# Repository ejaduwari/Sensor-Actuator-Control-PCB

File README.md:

# Sensor-Actuator-Control-PCB
STM32F103C8 carrier board controlling 6 stepper motors, servos, limit switches, and IO expanders with UART, SPI, and I2C interfaces. Includes full pin mapping, dual-regulator power design, and detailed failure analysis with debugging insights and hardware lessons learned.

# 📘 STM32F103C8 Stepper Motor Controller  
### Carrier Board + Small Pill Architecture & Debug Report

---

## 📑 Table of Contents
- [Overview](#overview)
- [Hardware Architecture](#hardware-architecture)
- [Pin Mapping (STM32 ↔ Carrier Board)](#pin-mapping-stm32--carrier-board)
- [Peripheral Interfaces](#peripheral-interfaces)
- [Clock & Crystal](#clock--crystal)
- [Power System Design](#power-system-design)
- [IO Expanders](#io-expanders)
- [Failure Report & Debugging](#failure-report--debugging)
- [Root Cause Analysis](#root-cause-analysis)
- [Current Status](#current-status)
- [Design Lessons & Prevention](#design-lessons--prevention)

---

## 🔍 Overview

This project is a **custom STM32F103C8-based PCB** designed to control:
- Multiple **A4988 stepper drivers**
- Several **servo outputs**
- External IO via expanders

The board uses a **Small Pill (STM32F103C8T6)** mounted on a **carrier board**, providing structured routing for motion control and expansion.

---

## 🧩 Hardware Architecture

- **MCU:** STM32F103C8T6 (Small Pill)
- **Motor Drivers:** A4988 (external)
- **IO Expansion:** PI4IOE5V6416
- **Power Inputs:**
  - USB (via L78L00 regulator)
  - External 5V (via AP2112K-3.3)
- **Control Signals:**
  - STEP / DIR for 6 axes
  - Servo PWM outputs
- **Debug Interface:**
  - SWD (SWCLK, SWDIO)

---

## 🔌 Pin Mapping (STM32 ↔ Carrier Board)

| STM32 Pin | Function |
|----------|--------|
| PA0 | 5_DIR |
| PA1 | 5_STP |
| PA2 | TX |
| PA3 | RX |
| PA4 | 1_DIR |
| PA5 | SCK |
| PA6 | MISO |
| PA7 | MOSI |
| PA8 | SERVO_1_3V3 |
| PA9 | SERVO_2_3V3 |
| PA10 | SERVO_3_3V3 |
| PA11 | USB- |
| PA12 | USB+ |
| PA15 | SERVO_4_3V3 |

| STM32 Pin | Function |
|----------|--------|
| PB0 | 4_STP |
| PB1 | 4_DIR |
| PB2 | BOOT |
| PB3 | 3_STP |
| PB4 | SERVO_6_3V3 |
| PB5 | SW9 |
| PB6 | SCL |
| PB7 | SDA |
| PB8 | 6_DIR |
| PB9 | SW10 |
| PB10 | 3_DIR |
| PB11 | 6_STP |
| PB12 | LED |
| PB13 | GPIO |
| PB14 | GPIO |
| PB15 | GPIO |

| STM32 Pin | Function |
|----------|--------|
| PC13 | 2_DIR |
| PC14 | 2_STP |
| PC15 | 1_STP |

| Debug Pins | Function |
|-----------|--------|
| PA13 | SWDIO |
| PA14 | SWCLK |
| NRST | Reset |

---

## 🔗 Peripheral Interfaces

### UART
- TX: PA2  
- RX: PA3  

### SPI
- SCK: PA5  
- MISO: PA6  
- MOSI: PA7  

### I2C
- SCL: PB6  
- SDA: PB7  

---

## ⏱ Clock & Crystal

- **Component:** 25 MHz SMD Crystal  
- **Capacitance:** 20pF  
- **Package:** 3.2mm × 2.5mm  

- **DigiKey Part #:** 3155-25M20P2/XT324-10/10CT-ND  
- **Manufacturer #:** 25M20P2/XT324-10/10  

---

## ⚡ Power System Design

### Regulators

**1. L78L00**
- Input: USB (~5V)
- Output: 3.3V (intended)
- Status: ❌ Damaged / unstable

**2. AP2112K-3.3**
- Input: External 5V
- Output: 3.3V
- Status: ✅ Functional

---

### Observed Behavior

- With motors connected:
  - 3.3V rail dropped to ~3.0V
- With L78L00 removed:
  - Stable 3.29V from AP2112K
- Backfeeding observed across regulators

---

## 🔌 IO Expanders

- **Model:** PI4IOE5V6416  
- Used for:
  - Microstepping control
  - Enable signals

⚠️ These lines interface with high-current drivers → risk area

---

## 🧪 Failure Report & Debugging

### Initial Symptoms

- PB12 LED stopped working
- MCU still flashable (initially)
- Reset did not recover functionality

---

### Voltage Measurements

| Condition | Observation |
|----------|------------|
| Motors connected | 3.3V ~3.0V |
| PB12 | ~0.12V |
| After disconnecting 12V | PB12 still ~0.12V |
| Reset held | 3.3V rises slightly |

---

### GPIO Testing

- PB12–PB15 stuck at ~0.12V
- PB15 toggle test failed
- Same issue after MCU replacement

---

### Regulator Testing

- L78L00:
  - Input ~4.8V
  - Output unstable / low
- AP2112K:
  - Output stable at ~3.29V

---

### Fuse

- 0685H9100-01 → OK (~0Ω)

---

### After L78L00 Removal

- System powered via AP2112K
- 3.3V stable
- ❌ Flashing failed:
  - Error in final launch sequence
  - Failed to start GDB server

---

## 🔎 Root Cause Analysis

### 1. GPIO Damage
- PB12–PB15 permanently stuck low
- Cause: **Backfeed / overvoltage from stepper drivers**
- Likely triggered by:
- Swapping motor wires while powered

---

### 2. Power Rail Instability
- L78L00 regulator damaged
- Caused rail drops under load

---

### 3. Regulator Conflict
- Backfeeding between regulators
- L78L00 became ineffective

---

### 4. Flashing Failure
- Likely due to:
- Unstable VDD reference
- Improper SWD voltage levels

---

## 📉 Current Status

- ❌ Original MCU damaged (GPIO bank failure)
- ⚠️ Replacement MCU still showing abnormal GPIO behavior
- ✅ AP2112K regulator working
- ❌ Board cannot be flashed
- ❌ System non-functional

---

## 🛠 Design Lessons & Prevention

### Critical Rules

- ❌ Never swap stepper wires under power
- ❌ Avoid direct MCU exposure to driver signals

---

### Recommended Fixes

- Add **series resistors** on control lines
- Use **optocouplers or buffers**
- Isolate **high-current paths**
- Ensure **single clean 3.3V source**
- Avoid regulator backfeeding

---

### Debug Best Practices

- Verify rails before applying load
- Test MCU pins before connecting drivers
- Use current limiting during bring-up

---

## 🚧 Final Note

This failure highlights a critical embedded design principle:

> **Power integrity and signal protection are just as important as logic design.**

Future revisions should prioritize:
- Electrical isolation
- Robust power architecture
- Safer bring-up procedures

---

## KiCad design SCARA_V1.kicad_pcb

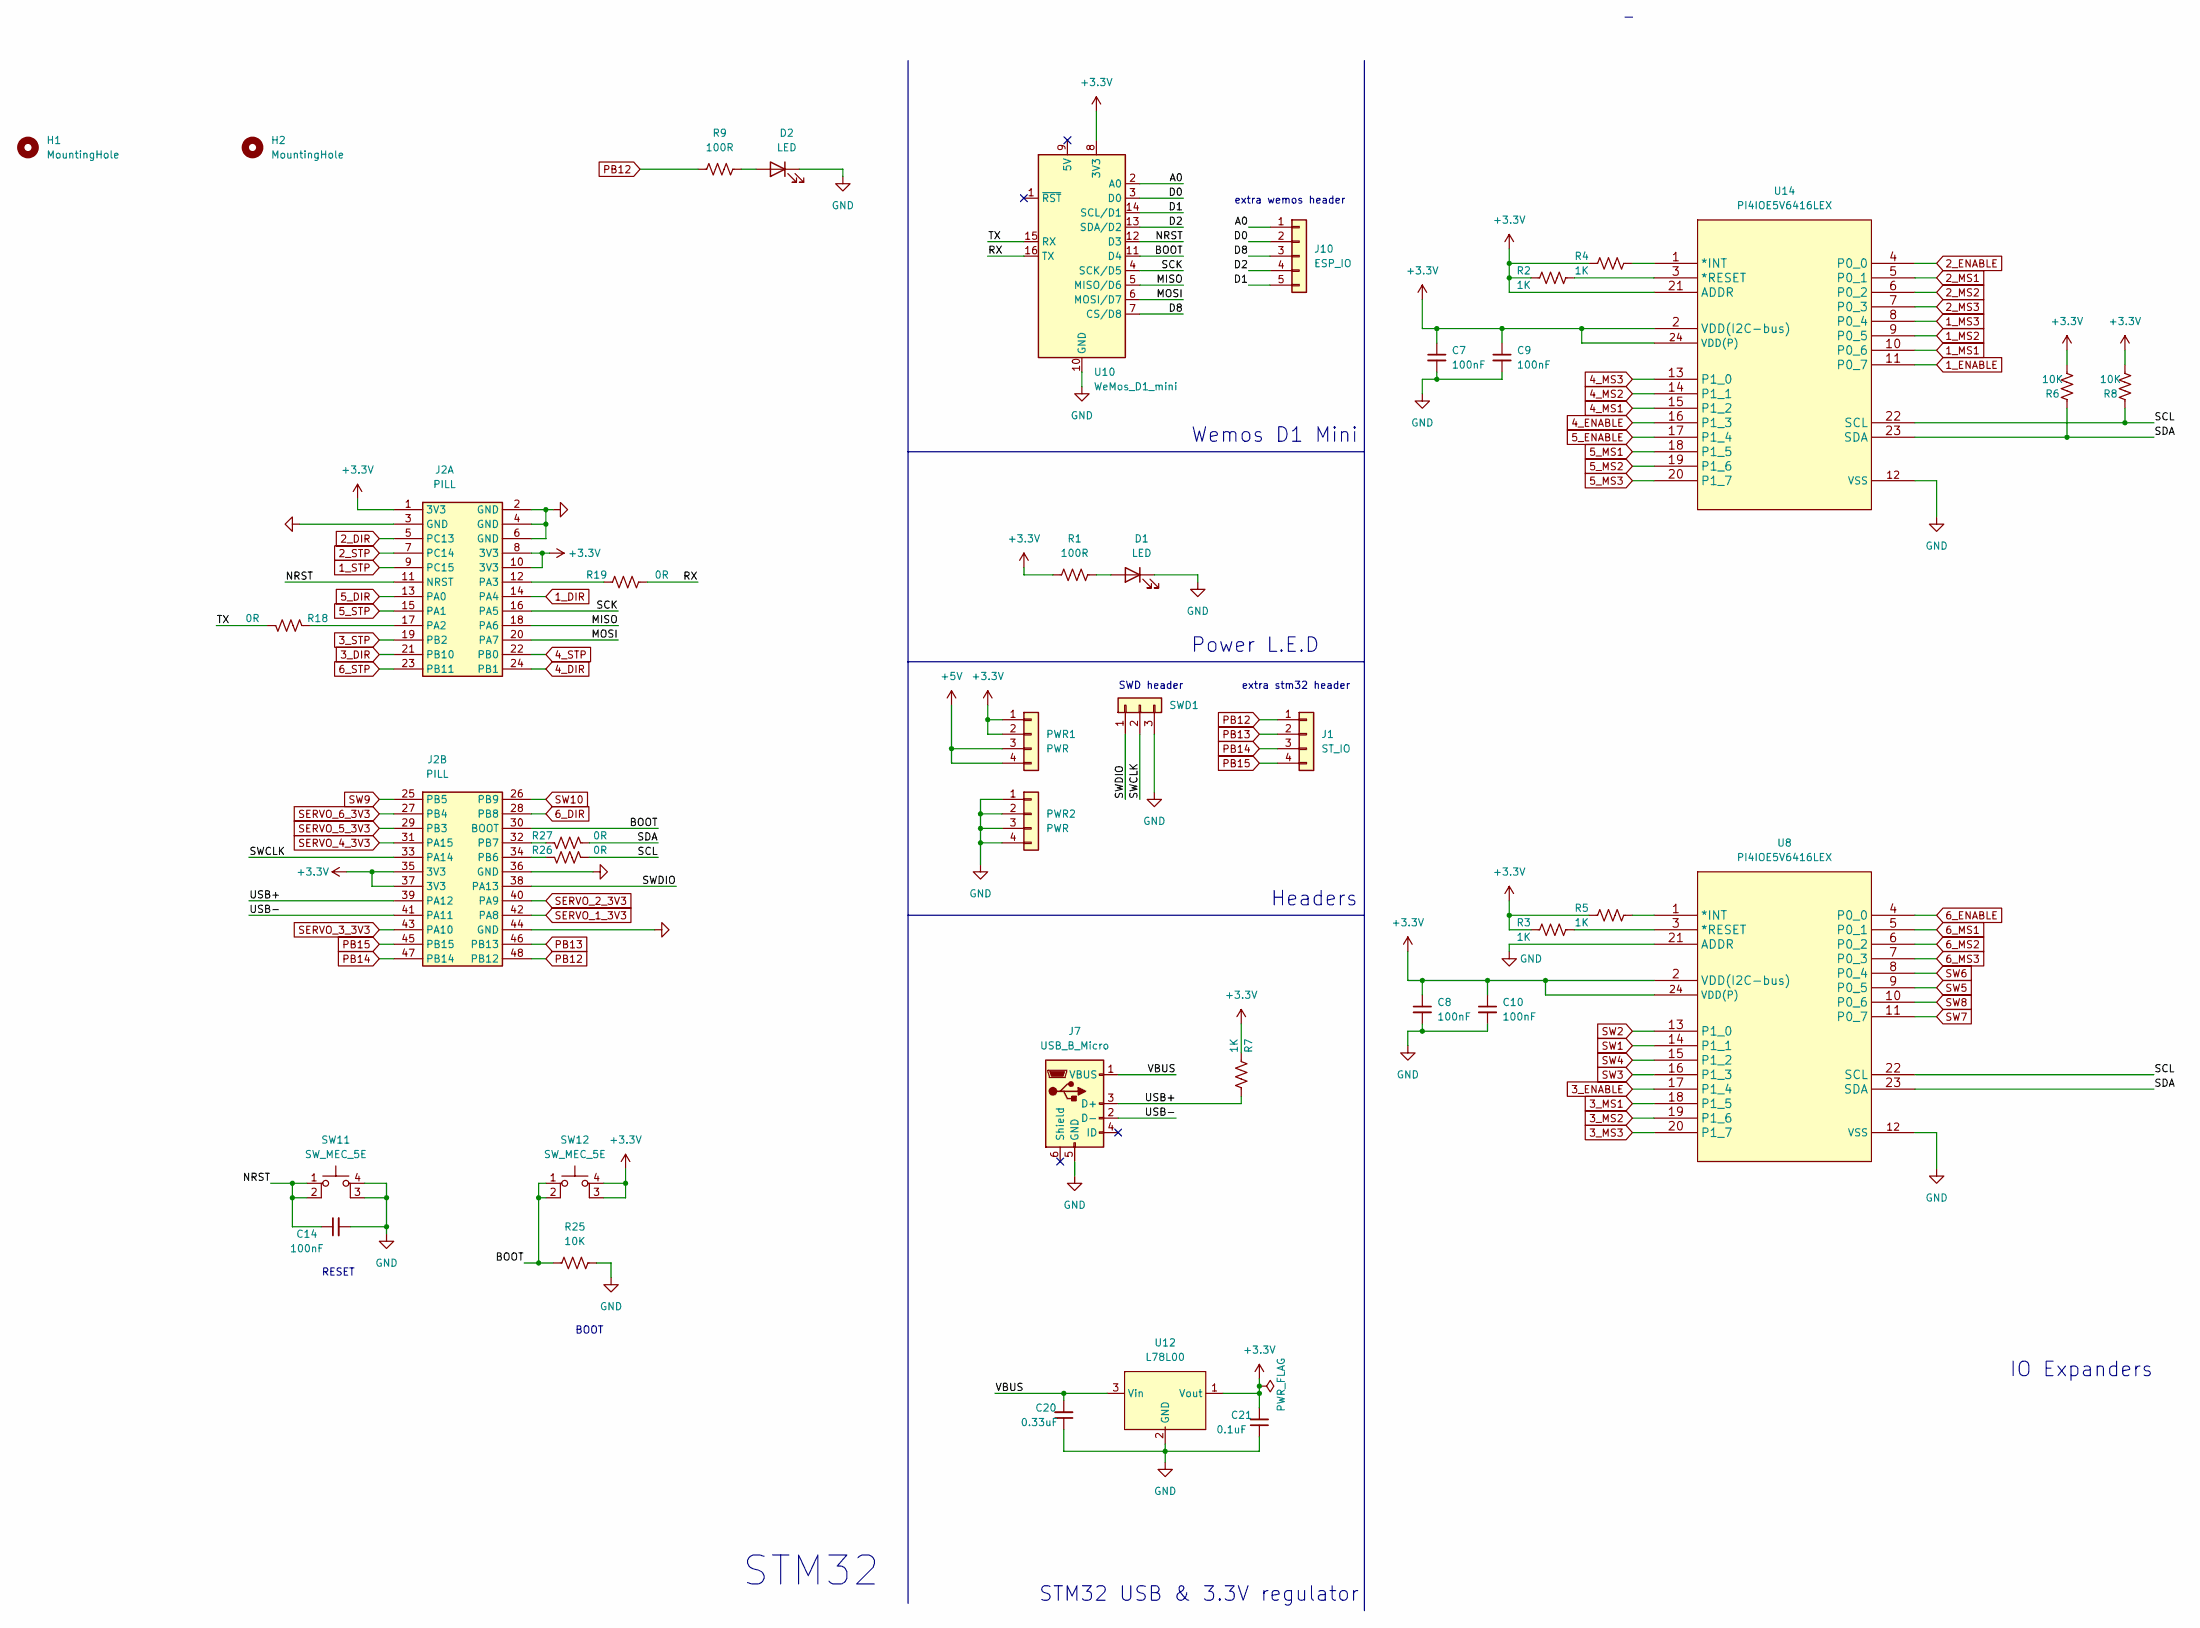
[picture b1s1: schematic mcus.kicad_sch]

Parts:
C7, C8, C9, C10: 100nF; C_0402_1005Metric
C14: 100nF; C_0805_2012Metric
C20: 0.33uF; C_0805_2012Metric_Pad1.18x1.45mm_HandSolder
C21: 0.1uF; C_0805_2012Metric_Pad1.18x1.45mm_HandSolder
D1, D2: LED; LED_0805_2012Metric
H1, H2: MountingHole; MountingHole_3.5mm
J1: ST_IO; PinHeader_1x04_P2.54mm_Vertical
J2: PILL
J7: USB_B_Micro; USB_Micro-B_Molex-105017-0001
J10: ESP_IO; PinHeader_1x05_P2.54mm_Vertical
PWR1, PWR2: PWR; PinHeader_1x04_P2.54mm_Vertical
R1, R9: 100R; R_0805_2012Metric
R2, R3, R4, R5, R7: 1K; R_0805_2012Metric
R6, R8, R25: 10K; R_0805_2012Metric
R18, R19, R26, R27: 0R; R_0805_2012Metric
SW11, SW12: SW_MEC_5E; PTS830GM140SMTRLFS
SWD1: Conn_01x03; PinHeader_1x03_P2.54mm_Vertical
U8, U14: PI4IOE5V6416LEX; TSSOP-24_4.4x7.8mm_P0.65mm
U10: WeMos_D1_mini; WEMOS_D1_mini_light
U12: L78L00; SOT-89-3

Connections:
1_DIR: J2.14 (PA4); also elsewhere on the board
1_ENABLE: U14.11 (P0_7); also elsewhere on the board
1_MS1: U14.10 (P0_6); also elsewhere on the board
1_MS2: U14.9 (P0_5); also elsewhere on the board
1_MS3: U14.8 (P0_4); also elsewhere on the board
1_STP: J2.9 (PC15); also elsewhere on the board
2_DIR: J2.5 (PC13); also elsewhere on the board
2_ENABLE: U14.4 (P0_0); also elsewhere on the board
2_MS1: U14.5 (P0_1); also elsewhere on the board
2_MS2: U14.6 (P0_2); also elsewhere on the board
2_MS3: U14.7 (P0_3); also elsewhere on the board
2_STP: J2.7 (PC14); also elsewhere on the board
3_DIR: J2.21 (PB10); also elsewhere on the board
3_ENABLE: U8.17 (P1_4); also elsewhere on the board
3_MS1: U8.18 (P1_5); also elsewhere on the board
3_MS2: U8.19 (P1_6); also elsewhere on the board
3_MS3: U8.20 (P1_7); also elsewhere on the board
3_STP: J2.19 (PB2); also elsewhere on the board
4_DIR: J2.24 (PB1); also elsewhere on the board
4_ENABLE: U14.16 (P1_3); also elsewhere on the board
4_MS1: U14.15 (P1_2); also elsewhere on the board
4_MS2: U14.14 (P1_1); also elsewhere on the board
4_MS3: U14.13 (P1_0); also elsewhere on the board
4_STP: J2.22 (PB0); also elsewhere on the board
5_DIR: J2.13 (PA0); also elsewhere on the board
5_ENABLE: U14.17 (P1_4); also elsewhere on the board
5_MS1: U14.18 (P1_5); also elsewhere on the board
5_MS2: U14.19 (P1_6); also elsewhere on the board
5_MS3: U14.20 (P1_7); also elsewhere on the board
5_STP: J2.15 (PA1); also elsewhere on the board
6_DIR: J2.28 (PB8); also elsewhere on the board
6_ENABLE: U8.4 (P0_0); also elsewhere on the board
6_MS1: U8.5 (P0_1); also elsewhere on the board
6_MS2: U8.6 (P0_2); also elsewhere on the board
6_MS3: U8.7 (P0_3); also elsewhere on the board
6_STP: J2.23 (PB11); also elsewhere on the board
+3.3V: C7.1, C8.1, C9.1, C10.1, C21.2, J2.1 (3V3), J2.8 (3V3), J2.10 (3V3), J2.35 (3V3), J2.37 (3V3), PWR1.1, PWR1.2, R1.1, R2.2, R3.2, R4.2, R5.2, R6.1, R7.2, R8.1, SW12.3 (K), SW12.4 (A), U8.2 (VDD(I2C-bus)), U8.24 (VDD(P)), U10.8 (3V3), U12.1 (Vout), U14.2 (VDD(I2C-bus)), U14.21 (ADDR), U14.24 (VDD(P)); also elsewhere on the board
+5V: PWR1.3, PWR1.4; also elsewhere on the board
/MCUs/A0: J10.1, U10.2 (A0)
/MCUs/BOOT: J2.30 (BOOT), R25.1, SW12.1, SW12.2, U10.11 (D4)
/MCUs/D0: J10.2, U10.3 (D0)
/MCUs/D1: J10.5, U10.14 (SCL/D1)
/MCUs/D2: J10.4, U10.13 (SDA/D2)
/MCUs/D8: J10.3, U10.7 (CS/D8)
/MCUs/MISO: J2.18 (PA6), U10.5 (MISO/D6)
/MCUs/MOSI: J2.20 (PA7), U10.6 (MOSI/D7)
/MCUs/NRST: C14.1, J2.11 (NRST), SW11.1, SW11.2, U10.12 (D3)
/MCUs/RX: R19.2, U10.16 (TX)
/MCUs/SCK: J2.16 (PA5), U10.4 (SCK/D5)
/MCUs/SCL: R8.2, R26.1, U8.22 (SCL), U14.22 (SCL)
/MCUs/SDA: R6.2, R27.1, U8.23 (SDA), U14.23 (SDA)
/MCUs/SWCLK: J2.33 (PA14), SWD1.2
/MCUs/SWDIO: J2.38 (PA13), SWD1.1
/MCUs/TX: R18.2, U10.15 (RX)
/MCUs/USB+: J2.39 (PA12), J7.3 (D+), R7.1
/MCUs/USB-: J2.41 (PA11), J7.2 (D-)
/MCUs/VBUS: C20.2, J7.1 (VBUS), U12.3 (Vin)
GND: C7.2, C8.2, C9.2, C10.2, C14.2, C20.1, C21.1, D1.1 (K), D2.1 (K), J2.2 (GND), J2.3 (GND), J2.4 (GND), J2.6 (GND), J2.36 (GND), J2.44 (GND), J7.5 (GND), PWR2.1, PWR2.2, PWR2.3, PWR2.4, R25.2, SW11.3 (K), SW11.4 (A), SWD1.3, U8.12 (VSS), U8.21 (ADDR), U10.10 (GND), U12.2 (GND), U14.12 (VSS); also elsewhere on the board
unnamed: D1.2 (A), R1.2
unnamed: D2.2 (A), R9.2
unnamed: J2.12 (PA3), R19.1
unnamed: J2.17 (PA2), R18.1
unnamed: J2.32 (PB7), R27.2
unnamed: J2.34 (PB6), R26.2
unnamed: R2.1, U14.3 (*RESET)
unnamed: R3.1, U8.3 (*RESET)
unnamed: R4.1, U14.1 (*INT)
unnamed: R5.1, U8.1 (*INT)
PB12: J1.1, J2.48 (PB12), R9.1
PB13: J1.2, J2.46 (PB13)
PB14: J1.3, J2.47 (PB14)
PB15: J1.4, J2.45 (PB15)
SERVO_1_3V3: J2.42 (PA8); also elsewhere on the board
SERVO_2_3V3: J2.40 (PA9); also elsewhere on the board
SERVO_3_3V3: J2.43 (PA10); also elsewhere on the board
SERVO_4_3V3: J2.31 (PA15); also elsewhere on the board
SERVO_5_3V3: J2.29 (PB3); also elsewhere on the board
SERVO_6_3V3: J2.27 (PB4); also elsewhere on the board
SW1: U8.14 (P1_1); also elsewhere on the board
SW2: U8.13 (P1_0); also elsewhere on the board
SW3: U8.16 (P1_3); also elsewhere on the board
SW4: U8.15 (P1_2); also elsewhere on the board
SW5: U8.9 (P0_5); also elsewhere on the board
SW6: U8.8 (P0_4); also elsewhere on the board
SW7: U8.11 (P0_7); also elsewhere on the board
SW8: U8.10 (P0_6); also elsewhere on the board
SW9: J2.25 (PB5); also elsewhere on the board
SW10: J2.26 (PB9); also elsewhere on the board

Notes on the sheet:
extra stm32 header
STM32
extra wemos header
SWD header
IO Expanders
Wemos D1 Mini
BOOT
STM32 USB & 3.3V regulator
RESET
Power L.E.D
Headers

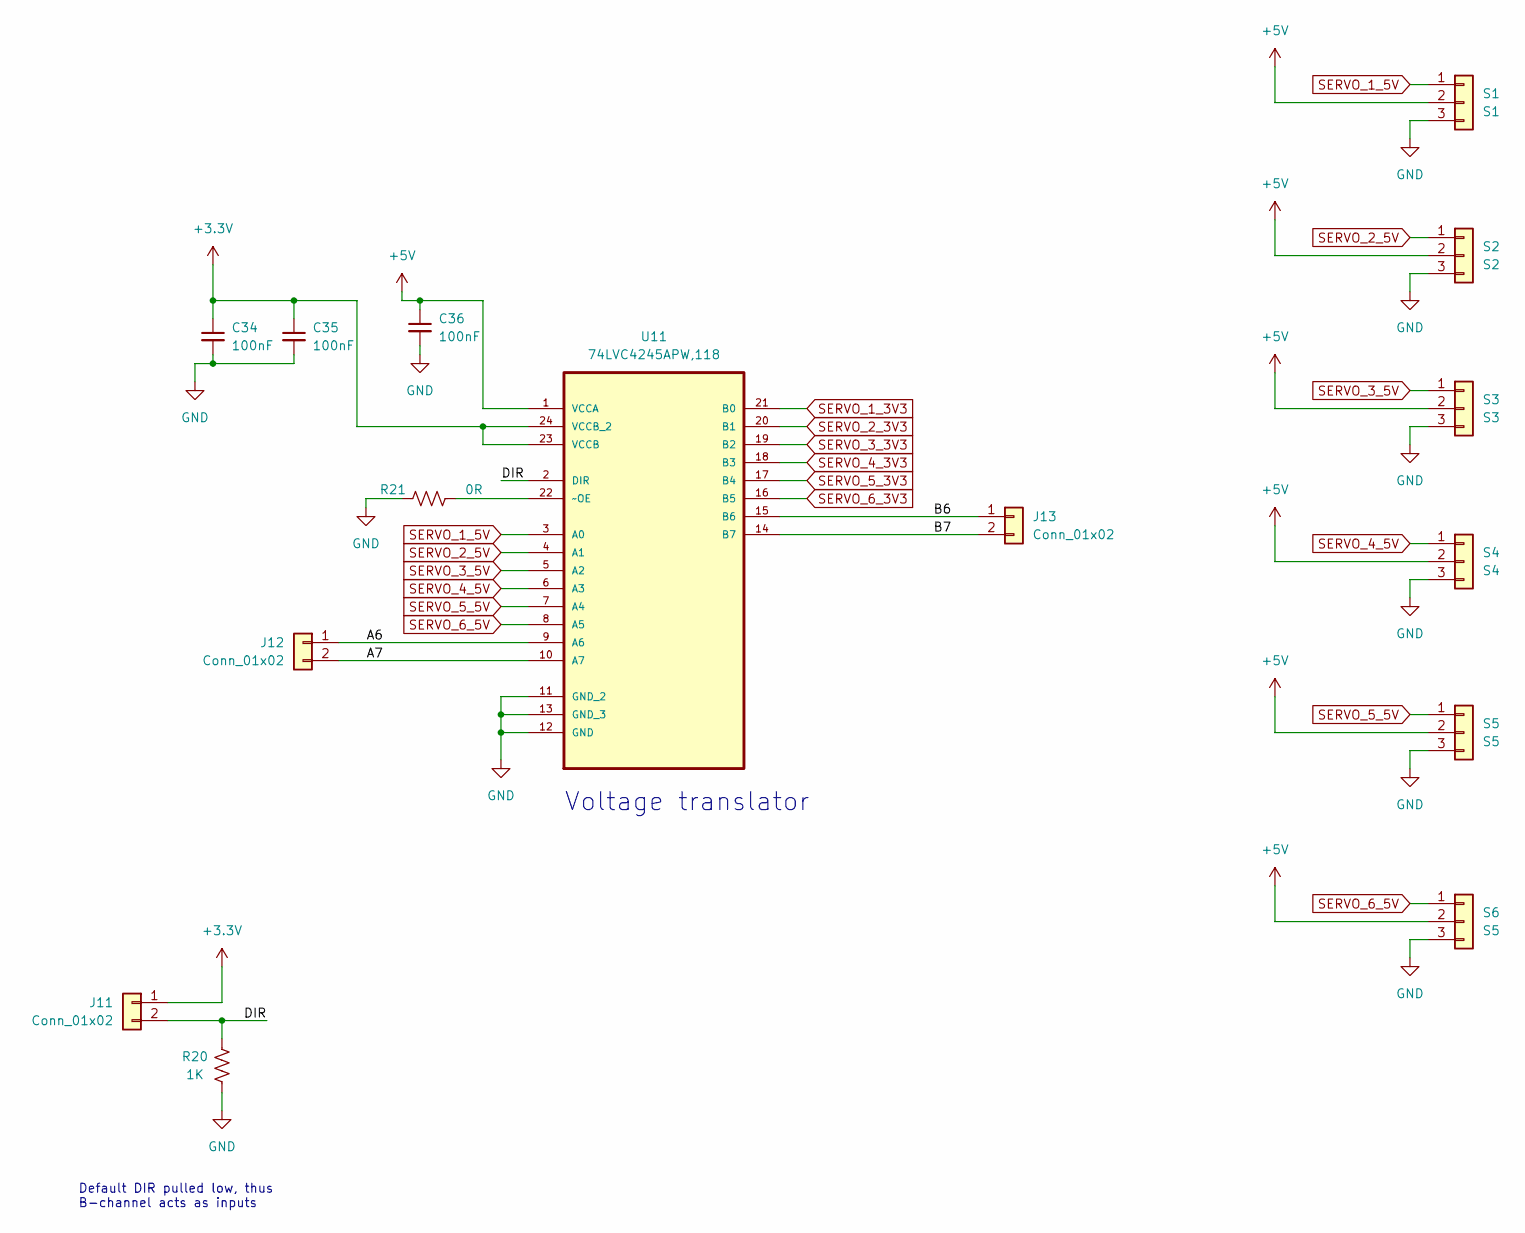
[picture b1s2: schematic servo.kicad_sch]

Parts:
C34, C35, C36: 100nF; C_0805_2012Metric
J11, J12, J13: Conn_01x02; PinHeader_1x02_P2.54mm_Vertical
R20: 1K; R_0805_2012Metric
R21: 0R; R_0805_2012Metric
S1: S1; PinHeader_1x03_P2.54mm_Vertical
S2: S2; PinHeader_1x03_P2.54mm_Vertical
S3: S3; PinHeader_1x03_P2.54mm_Vertical
S4: S4; PinHeader_1x03_P2.54mm_Vertical
S5, S6: S5; PinHeader_1x03_P2.54mm_Vertical
U11: 74LVC4245APW,118; SOP65P640X110-24N; MPN 74LVC4245APW,118

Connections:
+3.3V: C34.1, C35.1, J11.1, U11.23 (VCCB), U11.24 (VCCB_2); also elsewhere on the board
+5V: C36.1, S1.2, S2.2, S3.2, S4.2, S5.2, S6.2, U11.1 (VCCA); also elsewhere on the board
/SERVOS/A6: J12.1, U11.9 (A6)
/SERVOS/A7: J12.2, U11.10 (A7)
/SERVOS/B6: J13.1, U11.15 (B6)
/SERVOS/B7: J13.2, U11.14 (B7)
/SERVOS/DIR: J11.2, R20.2, U11.2 (DIR)
GND: C34.2, C35.2, C36.2, R20.1, R21.1, S1.3, S2.3, S3.3, S4.3, S5.3, S6.3, U11.11 (GND_2), U11.12 (GND), U11.13 (GND_3); also elsewhere on the board
unnamed: R21.2, U11.22 (~OE)
SERVO_1_3V3: U11.21 (B0); also elsewhere on the board
SERVO_1_5V: S1.1, U11.3 (A0)
SERVO_2_3V3: U11.20 (B1); also elsewhere on the board
SERVO_2_5V: S2.1, U11.4 (A1)
SERVO_3_3V3: U11.19 (B2); also elsewhere on the board
SERVO_3_5V: S3.1, U11.5 (A2)
SERVO_4_3V3: U11.18 (B3); also elsewhere on the board
SERVO_4_5V: S4.1, U11.6 (A3)
SERVO_5_3V3: U11.17 (B4); also elsewhere on the board
SERVO_5_5V: S5.1, U11.7 (A4)
SERVO_6_3V3: U11.16 (B5); also elsewhere on the board
SERVO_6_5V: S6.1, U11.8 (A5)

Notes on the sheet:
Default DIR pulled low, thus B-channel acts as inputs
Voltage translator

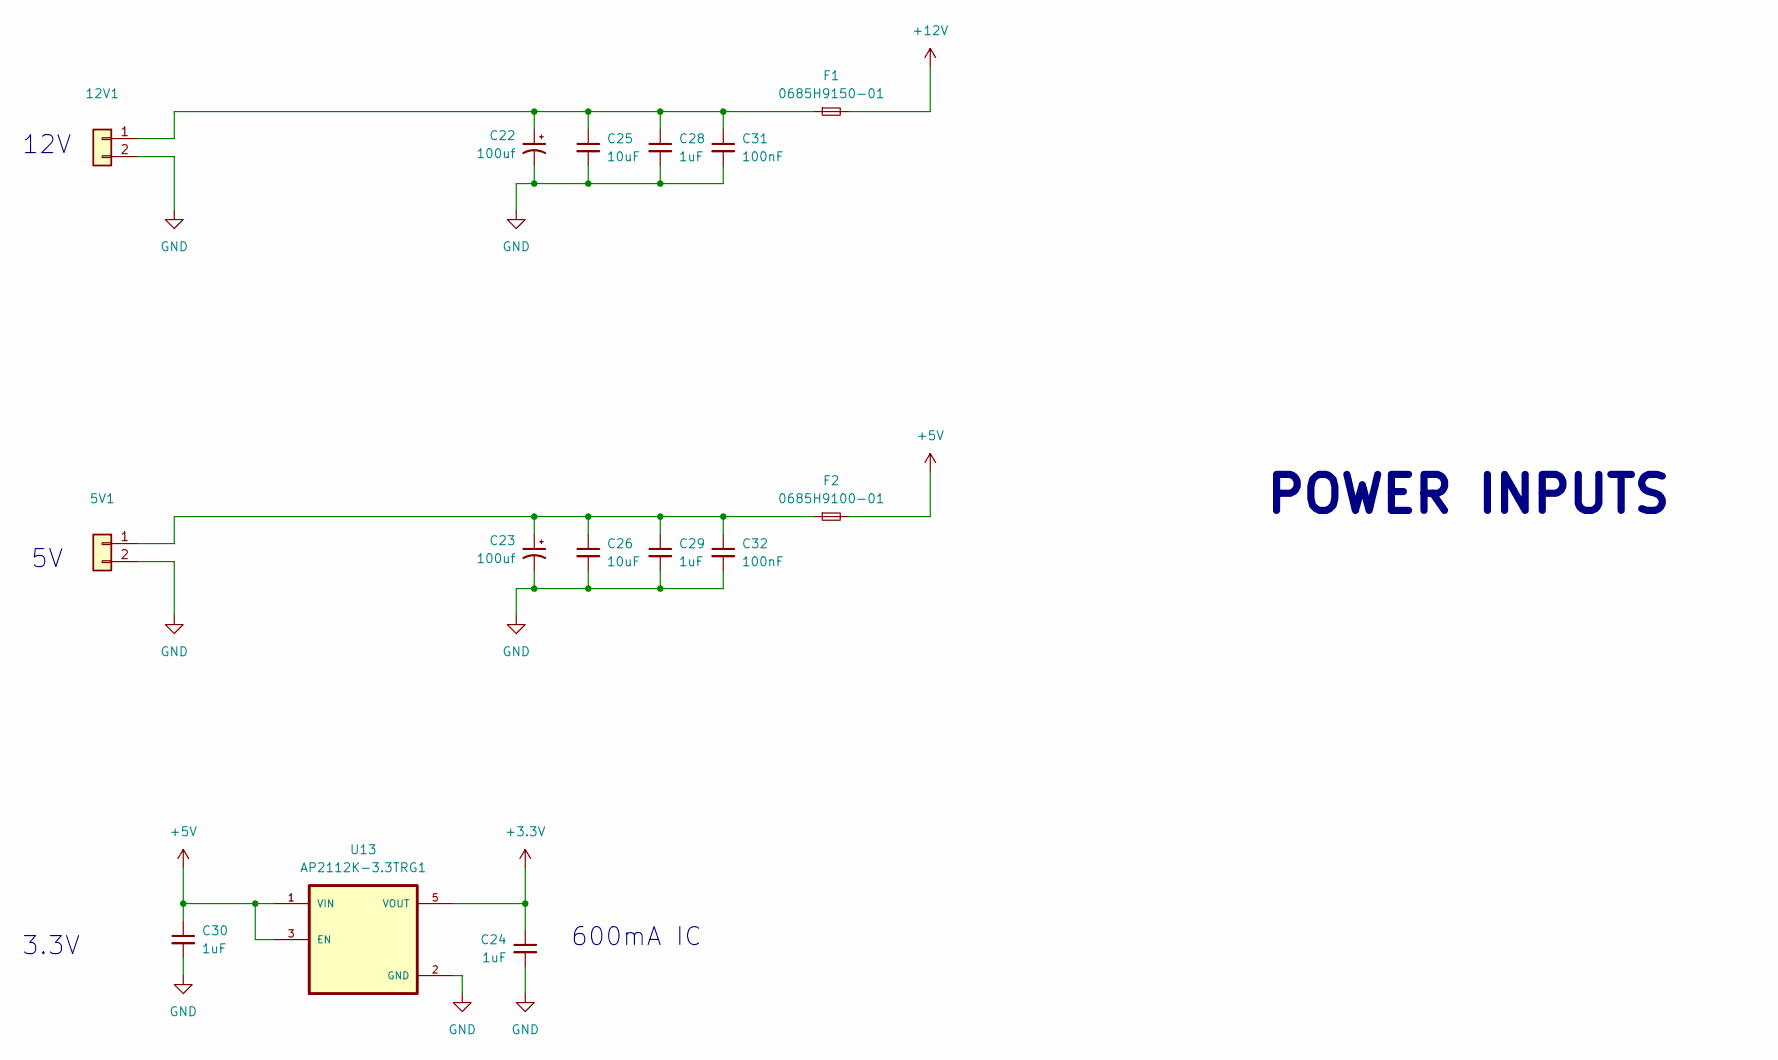
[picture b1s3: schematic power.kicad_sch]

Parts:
5V1, 12V1: Conn_01x02; PinHeader_1x02_P2.54mm_Vertical
C22, C23: 100uf; CP_Radial_D6.3mm_P2.50mm
C24, C28, C29, C30: 1uF; C_0805_2012Metric
C25, C26: 10uF; C_0805_2012Metric
C31, C32: 100nF; C_0805_2012Metric
F1: 0685H9150-01; 3.2x1.58
F2: 0685H9100-01; 3.2x1.58
U13: AP2112K-3.3TRG1; SOT95P285X140-5N; PARTREV 2-2

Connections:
+3.3V: C24.1, U13.5 (VOUT); also elsewhere on the board
+5V: C30.1, F2.2, U13.1 (VIN), U13.3 (EN); also elsewhere on the board
+12V: F1.2; also elsewhere on the board
GND: 5V1.2, 12V1.2, C22.2, C23.2, C24.2, C25.2, C26.2, C28.2, C29.2, C30.2, C31.2, C32.2, U13.2 (GND); also elsewhere on the board
unnamed: 5V1.1, C23.1, C26.1, C29.1, C32.1, F2.1
unnamed: 12V1.1, C22.1, C25.1, C28.1, C31.1, F1.1

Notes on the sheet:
600mA IC
12V
POWER INPUTS
3.3V

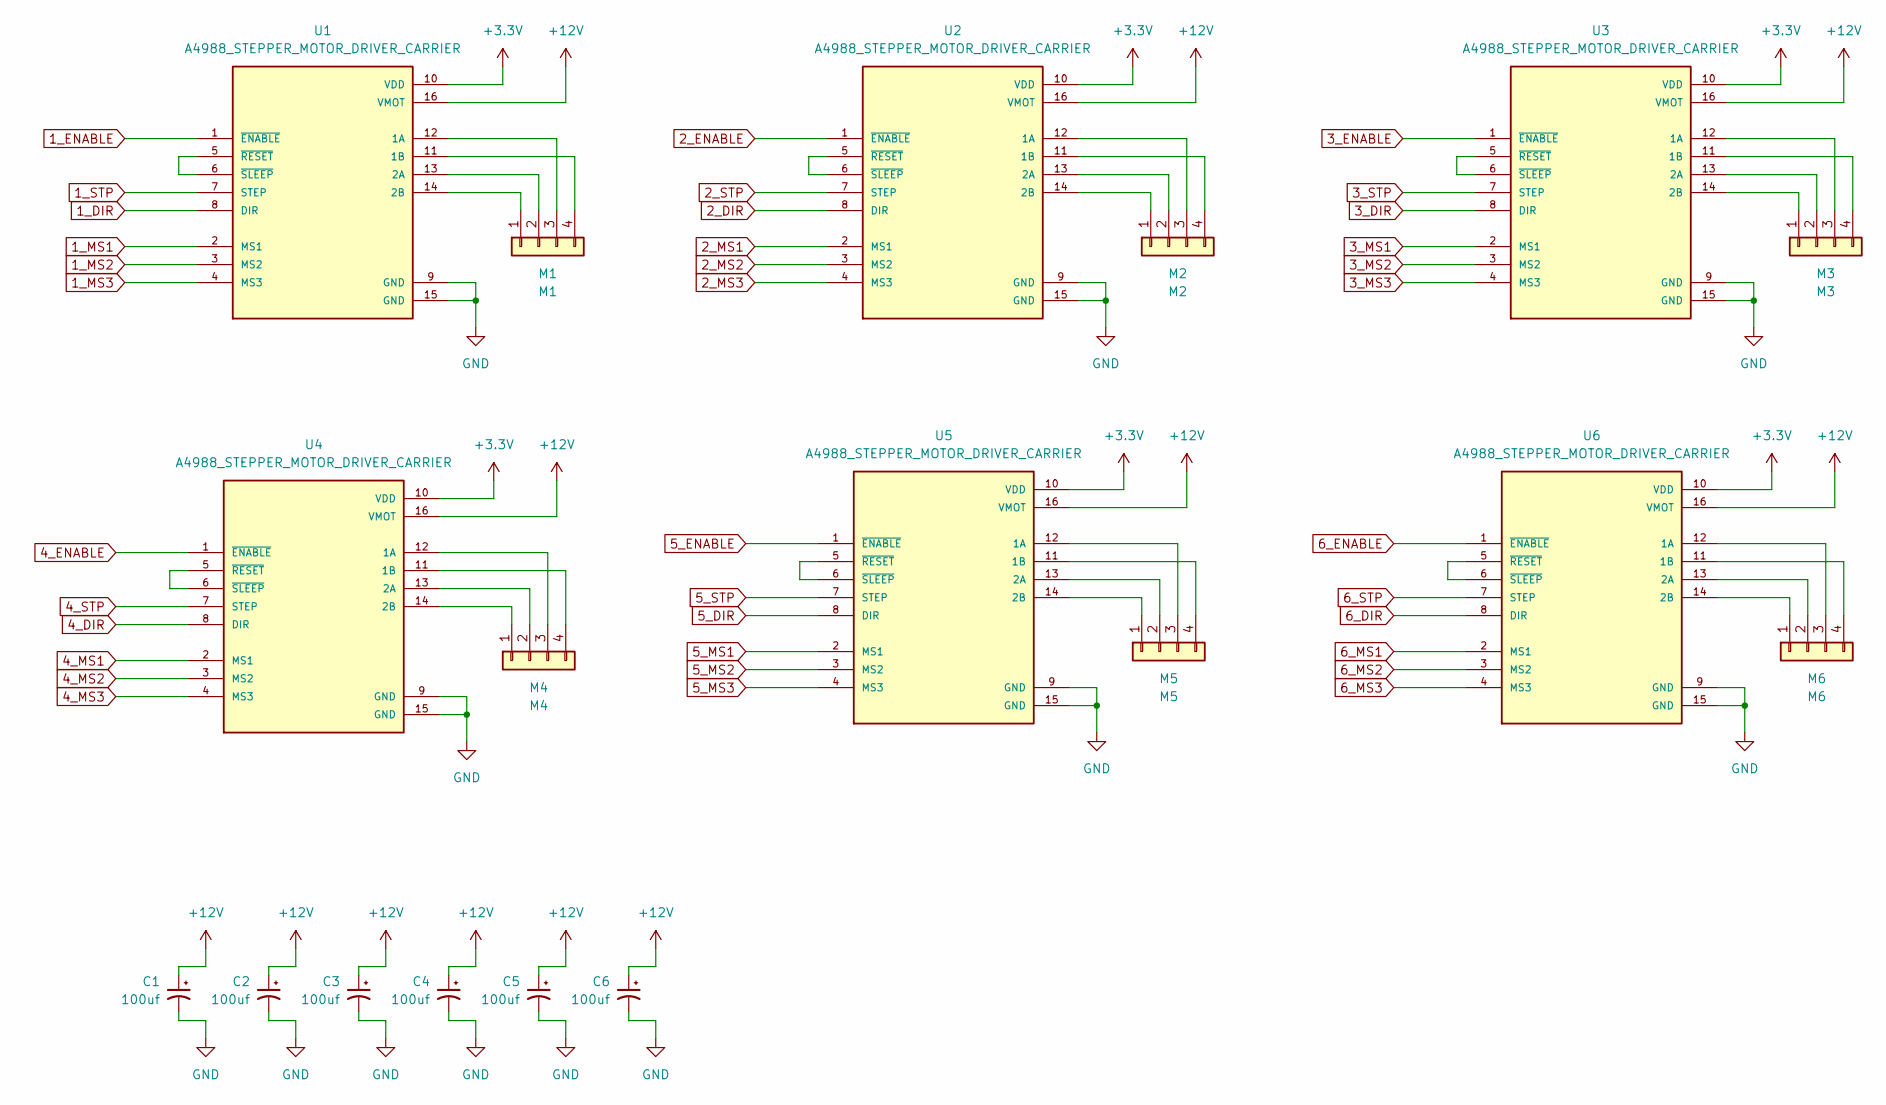
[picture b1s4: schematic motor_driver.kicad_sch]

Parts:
C1, C2, C3, C4, C5, C6: 100uf; CP_Radial_D6.3mm_P2.50mm
M1: M1; PinHeader_1x04_P2.54mm_Vertical
M2: M2; PinHeader_1x04_P2.54mm_Vertical
M3: M3; PinHeader_1x04_P2.54mm_Vertical
M4: M4; PinHeader_1x04_P2.54mm_Vertical
M5: M5; PinHeader_1x04_P2.54mm_Vertical
M6: M6; PinHeader_1x04_P2.54mm_Vertical
U1, U2, U3, U4, U5, U6: A4988_STEPPER_MOTOR_DRIVER_CARRIER; MODULE_A4988_STEPPER_MOTOR_DRIVER_CARRIER

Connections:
1_DIR: U1.8 (DIR); also elsewhere on the board
1_ENABLE: U1.1 (~ENABLE); also elsewhere on the board
1_MS1: U1.2 (MS1); also elsewhere on the board
1_MS2: U1.3 (MS2); also elsewhere on the board
1_MS3: U1.4 (MS3); also elsewhere on the board
1_STP: U1.7 (STEP); also elsewhere on the board
2_DIR: U2.8 (DIR); also elsewhere on the board
2_ENABLE: U2.1 (~ENABLE); also elsewhere on the board
2_MS1: U2.2 (MS1); also elsewhere on the board
2_MS2: U2.3 (MS2); also elsewhere on the board
2_MS3: U2.4 (MS3); also elsewhere on the board
2_STP: U2.7 (STEP); also elsewhere on the board
3_DIR: U3.8 (DIR); also elsewhere on the board
3_ENABLE: U3.1 (~ENABLE); also elsewhere on the board
3_MS1: U3.2 (MS1); also elsewhere on the board
3_MS2: U3.3 (MS2); also elsewhere on the board
3_MS3: U3.4 (MS3); also elsewhere on the board
3_STP: U3.7 (STEP); also elsewhere on the board
4_DIR: U4.8 (DIR); also elsewhere on the board
4_ENABLE: U4.1 (~ENABLE); also elsewhere on the board
4_MS1: U4.2 (MS1); also elsewhere on the board
4_MS2: U4.3 (MS2); also elsewhere on the board
4_MS3: U4.4 (MS3); also elsewhere on the board
4_STP: U4.7 (STEP); also elsewhere on the board
5_DIR: U5.8 (DIR); also elsewhere on the board
5_ENABLE: U5.1 (~ENABLE); also elsewhere on the board
5_MS1: U5.2 (MS1); also elsewhere on the board
5_MS2: U5.3 (MS2); also elsewhere on the board
5_MS3: U5.4 (MS3); also elsewhere on the board
5_STP: U5.7 (STEP); also elsewhere on the board
6_DIR: U6.8 (DIR); also elsewhere on the board
6_ENABLE: U6.1 (~ENABLE); also elsewhere on the board
6_MS1: U6.2 (MS1); also elsewhere on the board
6_MS2: U6.3 (MS2); also elsewhere on the board
6_MS3: U6.4 (MS3); also elsewhere on the board
6_STP: U6.7 (STEP); also elsewhere on the board
+3.3V: U1.10 (VDD), U2.10 (VDD), U3.10 (VDD), U4.10 (VDD), U5.10 (VDD), U6.10 (VDD); also elsewhere on the board
+12V: C1.1, C2.1, C3.1, C4.1, C5.1, C6.1, U1.16 (VMOT), U2.16 (VMOT), U3.16 (VMOT), U4.16 (VMOT), U5.16 (VMOT), U6.16 (VMOT); also elsewhere on the board
GND: C1.2, C2.2, C3.2, C4.2, C5.2, C6.2, U1.9 (GND), U1.15 (GND), U2.9 (GND), U2.15 (GND), U3.9 (GND), U3.15 (GND), U4.9 (GND), U4.15 (GND), U5.9 (GND), U5.15 (GND), U6.9 (GND), U6.15 (GND); also elsewhere on the board
unnamed: M1.1, U1.14 (2B)
unnamed: M1.2, U1.13 (2A)
unnamed: M1.3, U1.12 (1A)
unnamed: M1.4, U1.11 (1B)
unnamed: M2.1, U2.14 (2B)
unnamed: M2.2, U2.13 (2A)
unnamed: M2.3, U2.12 (1A)
unnamed: M2.4, U2.11 (1B)
unnamed: M3.1, U3.14 (2B)
unnamed: M3.2, U3.13 (2A)
unnamed: M3.3, U3.12 (1A)
unnamed: M3.4, U3.11 (1B)
unnamed: M4.1, U4.14 (2B)
unnamed: M4.2, U4.13 (2A)
unnamed: M4.3, U4.12 (1A)
unnamed: M4.4, U4.11 (1B)
unnamed: M5.1, U5.14 (2B)
unnamed: M5.2, U5.13 (2A)
unnamed: M5.3, U5.12 (1A)
unnamed: M5.4, U5.11 (1B)
unnamed: M6.1, U6.14 (2B)
unnamed: M6.2, U6.13 (2A)
unnamed: M6.3, U6.12 (1A)
unnamed: M6.4, U6.11 (1B)
unnamed: U1.5 (~RESET), U1.6 (~SLEEP)
unnamed: U2.5 (~RESET), U2.6 (~SLEEP)
unnamed: U3.5 (~RESET), U3.6 (~SLEEP)
unnamed: U4.5 (~RESET), U4.6 (~SLEEP)
unnamed: U5.5 (~RESET), U5.6 (~SLEEP)
unnamed: U6.5 (~RESET), U6.6 (~SLEEP)

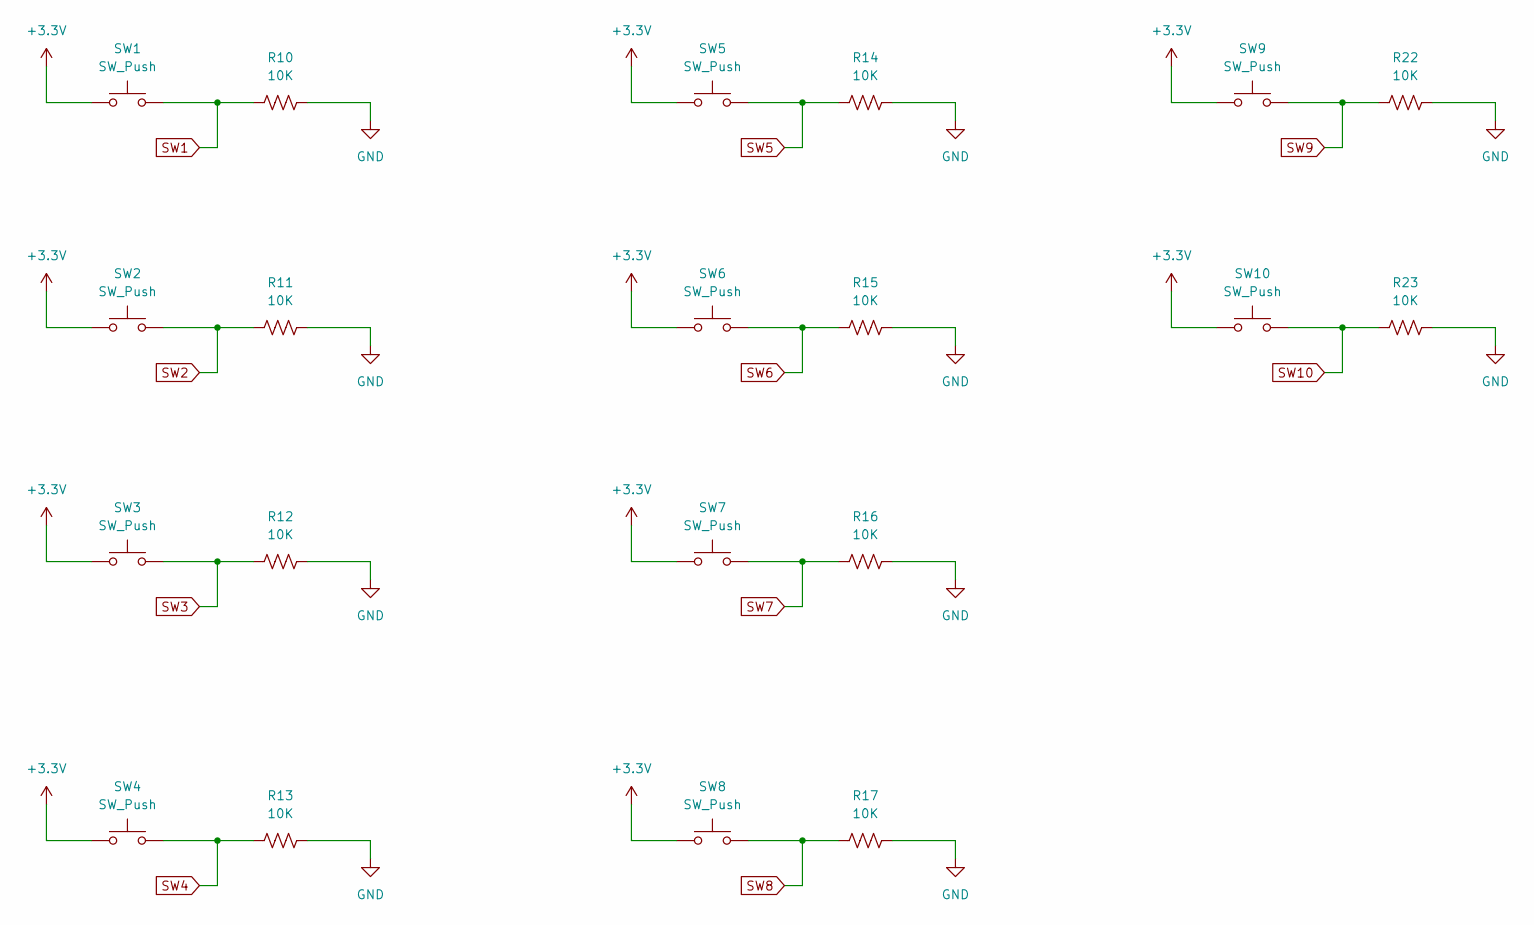
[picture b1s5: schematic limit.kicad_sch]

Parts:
R10, R11, R12, R13, R14, R15, R16, R17, R22, R23: 10K; R_0805_2012Metric
SW1, SW2, SW3, SW4, SW5, SW6, SW7, SW8, SW9, SW10: SW_Push; PinHeader_1x02_P2.54mm_Vertical

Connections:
+3.3V: SW1.1, SW2.1, SW3.1, SW4.1, SW5.1, SW6.1, SW7.1, SW8.1, SW9.1, SW10.1; also elsewhere on the board
GND: R10.2, R11.2, R12.2, R13.2, R14.2, R15.2, R16.2, R17.2, R22.2, R23.2; also elsewhere on the board
SW1: R10.1, SW1.2; also elsewhere on the board
SW2: R11.1, SW2.2; also elsewhere on the board
SW3: R12.1, SW3.2; also elsewhere on the board
SW4: R13.1, SW4.2; also elsewhere on the board
SW5: R14.1, SW5.2; also elsewhere on the board
SW6: R15.1, SW6.2; also elsewhere on the board
SW7: R16.1, SW7.2; also elsewhere on the board
SW8: R17.1, SW8.2; also elsewhere on the board
SW9: R22.1, SW9.2; also elsewhere on the board
SW10: R23.1, SW10.2; also elsewhere on the board

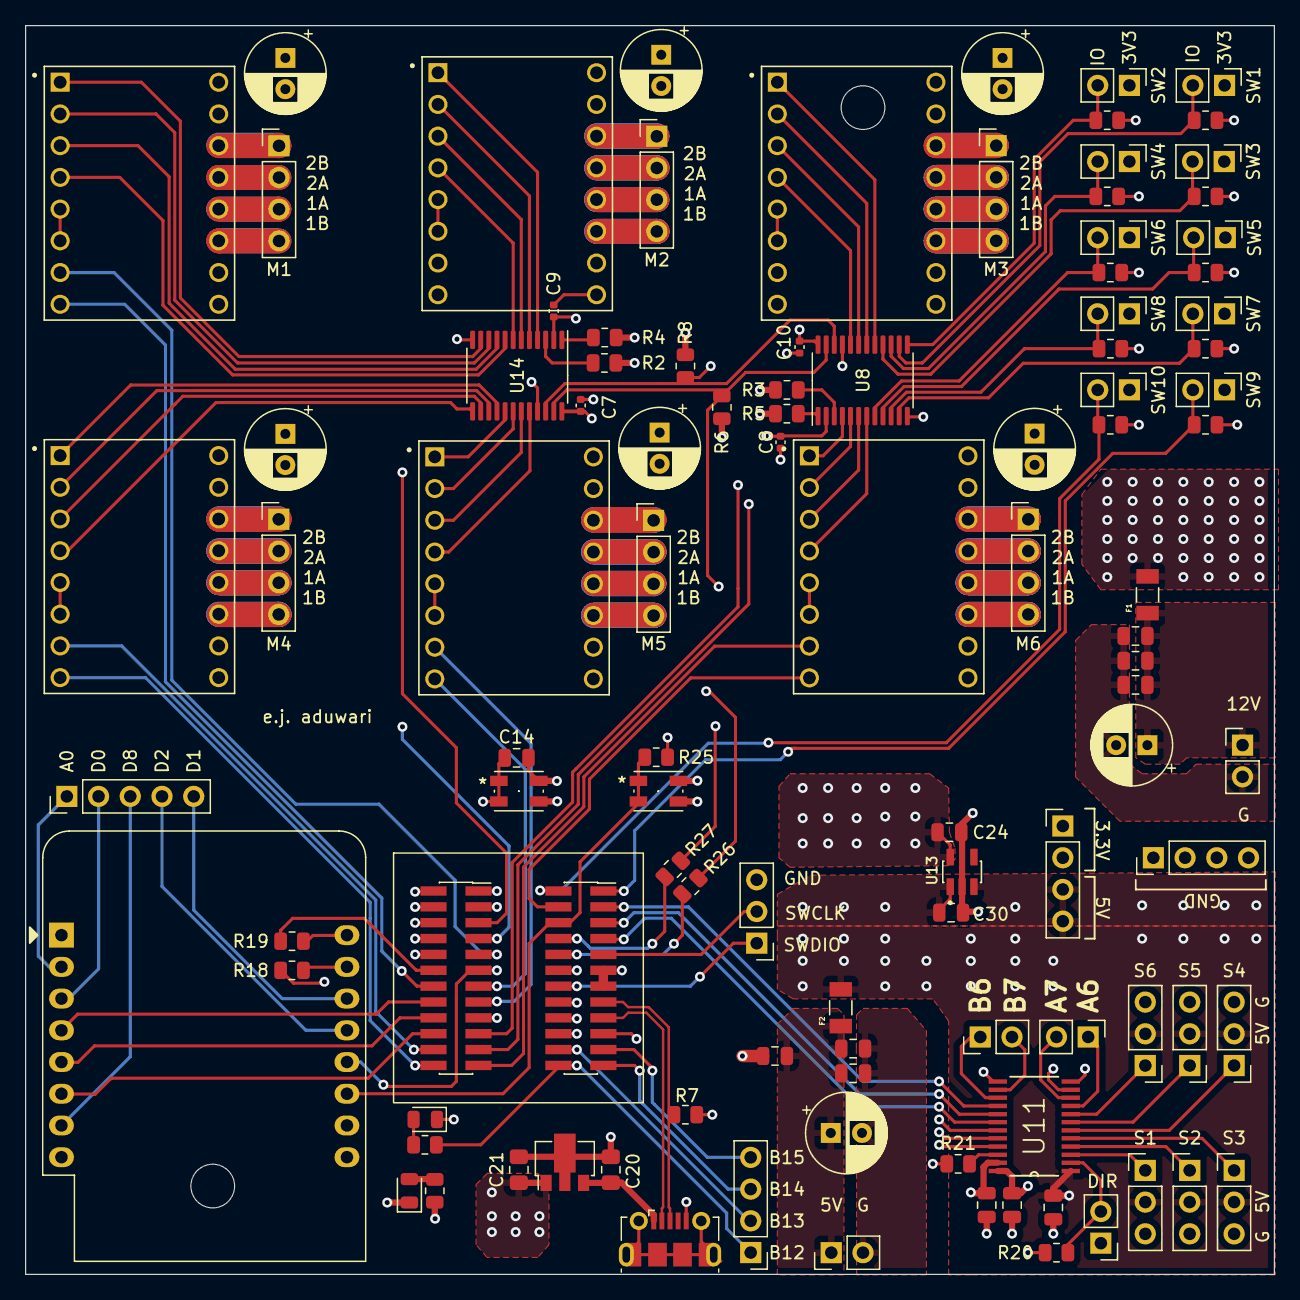
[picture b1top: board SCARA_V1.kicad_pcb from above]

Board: 4 copper layers, 100.0 x 100.0 mm, 106 parts (0 on the bottom side), 133 nets.
